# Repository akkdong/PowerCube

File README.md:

PowerCube
- Power Bank
- GPS
- Variometer
- Bluetooth

Goal: Charge mobile phone while transmitting GPS & Variometer data. It can also support BT connectivity.

<br>
<br>
<center>

</center>

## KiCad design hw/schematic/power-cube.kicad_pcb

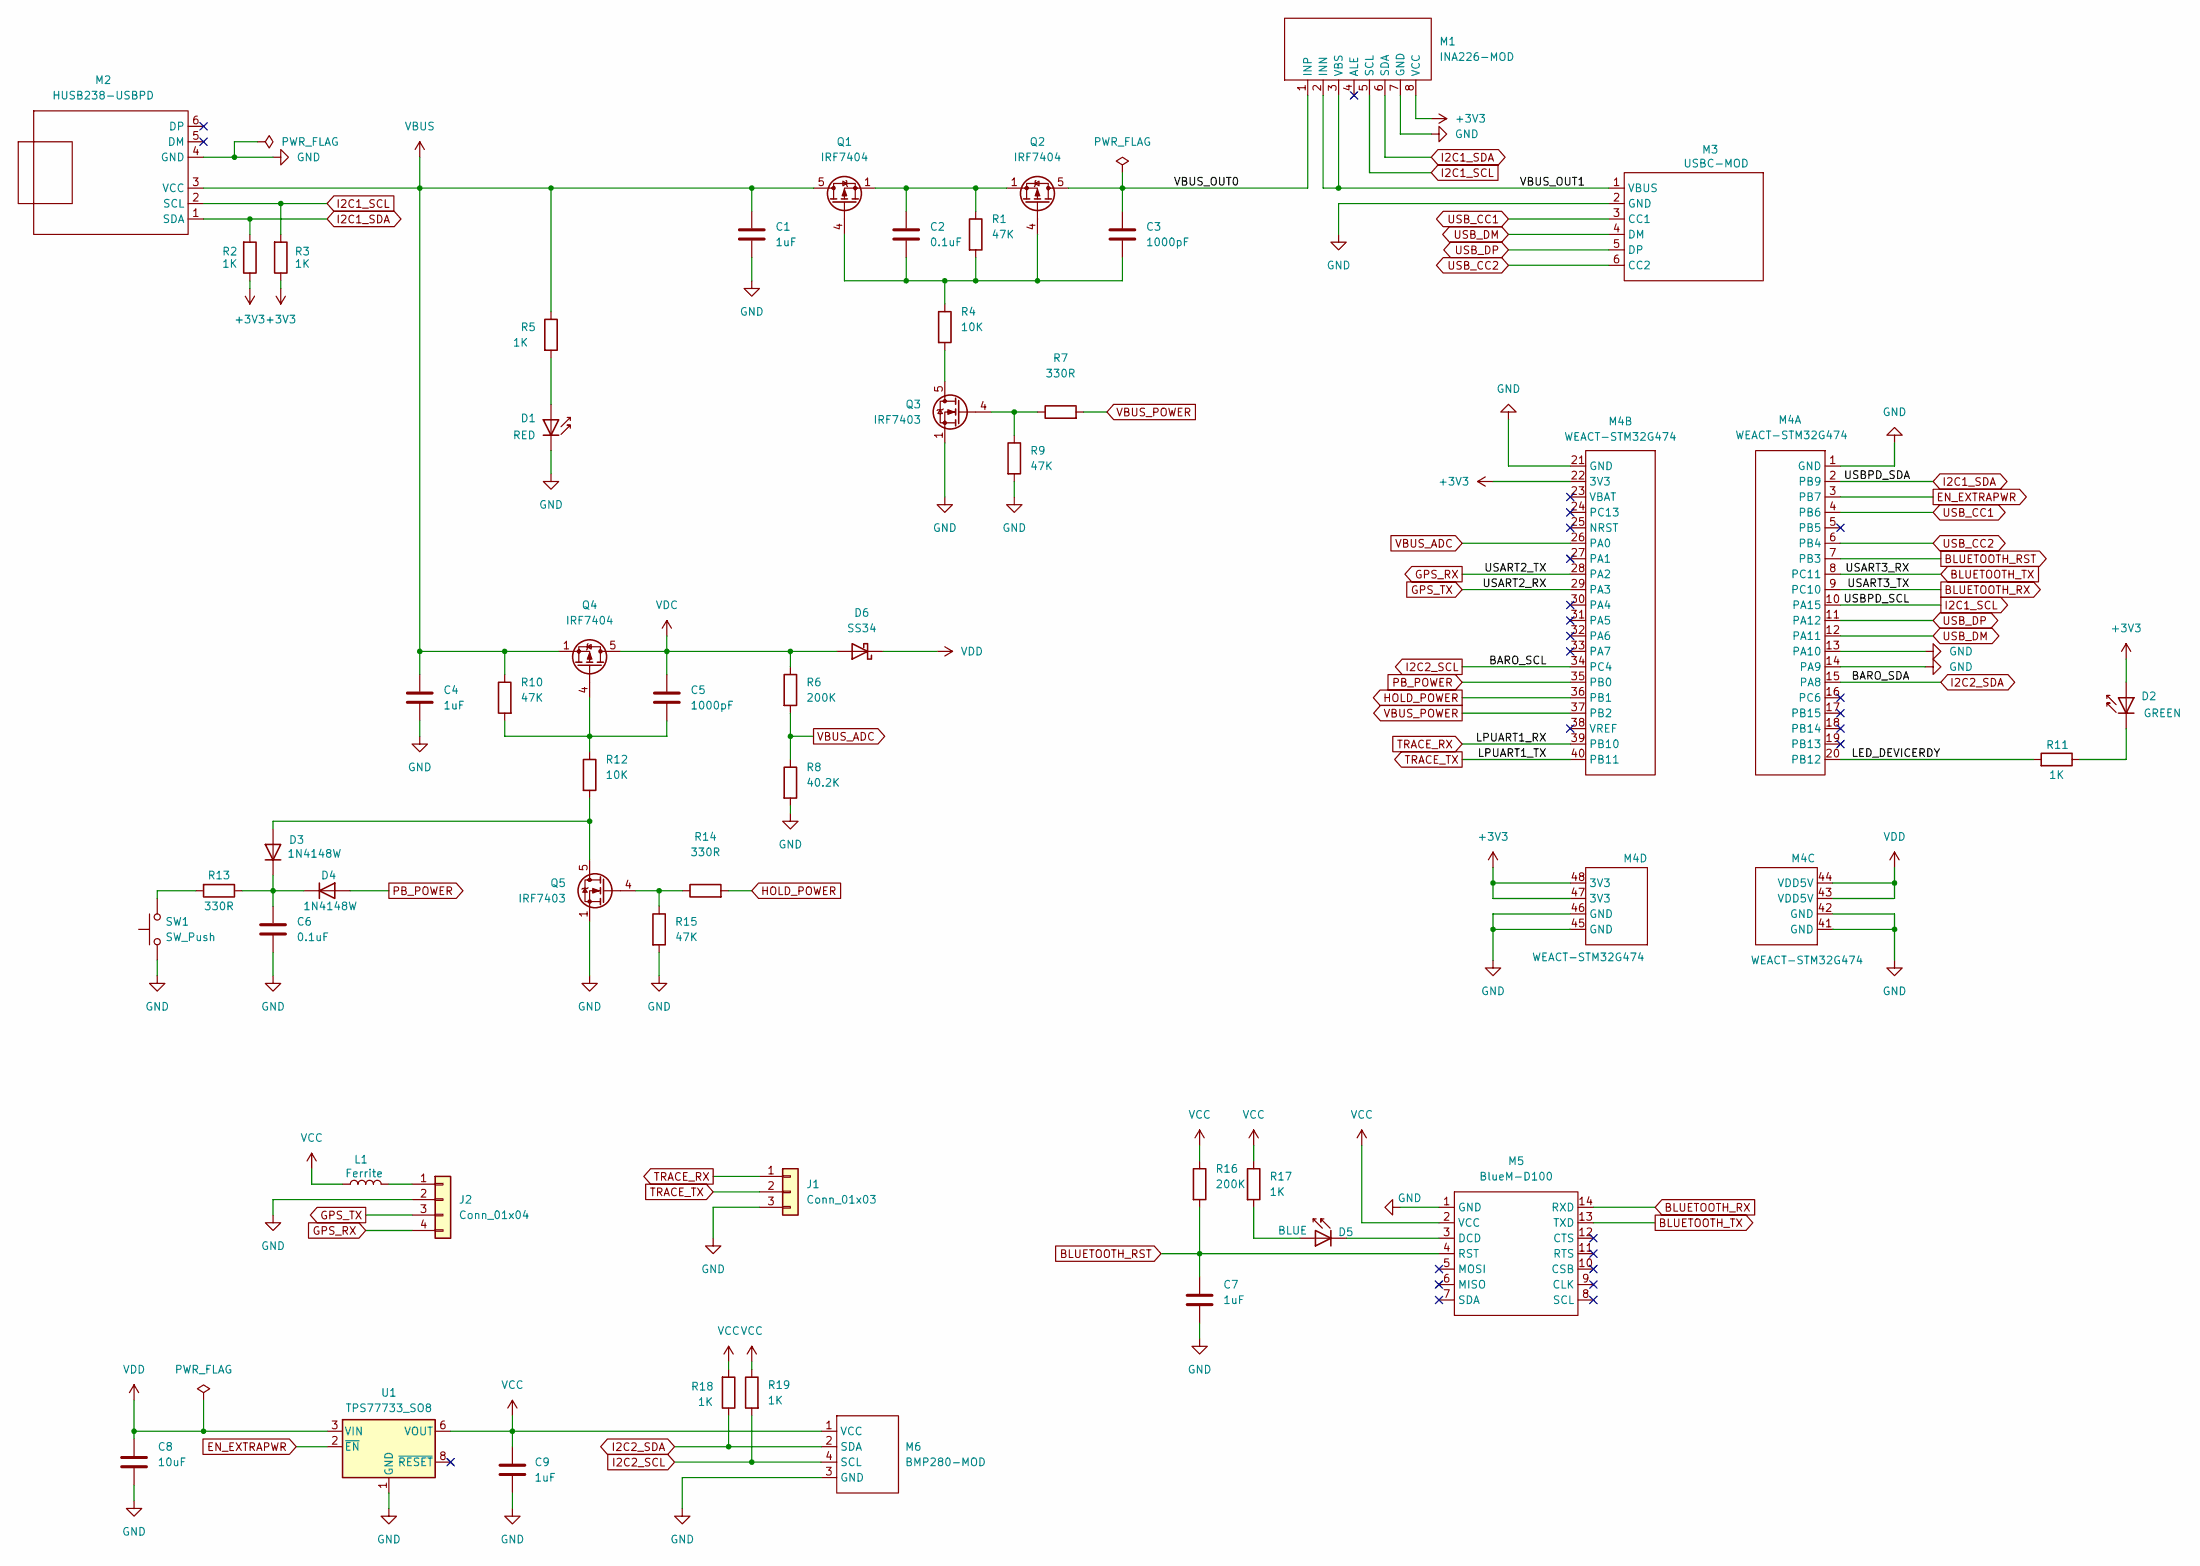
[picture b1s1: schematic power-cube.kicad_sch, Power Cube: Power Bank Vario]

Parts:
C1, C4, C7, C9: 1uF; C_0805_2012Metric_Pad1.18x1.45mm_HandSolder
C2, C6: 0.1uF; C_0805_2012Metric_Pad1.18x1.45mm_HandSolder
C3, C5: 1000pF; C_0805_2012Metric_Pad1.18x1.45mm_HandSolder
C8: 10uF; C_0805_2012Metric_Pad1.18x1.45mm_HandSolder
D1: RED; LED_0805_2012Metric_Pad1.15x1.40mm_HandSolder
D2: GREEN; LED_D3.0mm_Horizontal_O1.27mm_Z6.0mm
D3, D4: 1N4148W; D_SOD-123
D5: BLUE; LED_0805_2012Metric_Pad1.15x1.40mm_HandSolder
D6: SS34; D_SMA
J1: Conn_01x03; PinHeader_1x03_P2.54mm_Vertical
J2: Conn_01x04; GOOUUU-GPS-BD
L1: Ferrite; L_Axial_L5.3mm_D2.2mm_P10.16mm_Horizontal_Vishay_IM-1
M1: INA226-MOD
M2: HUSB238-USBPD
M3: USBC-MOD
M4: WEACT-STM32G474; WEACT-STM32G747
M5: BlueM-D100
M6: BMP280-MOD
Q1, Q2, Q4: IRF7404; DIP-8_W7.62mm_Socket
Q3, Q5: IRF7403; DIP-8_W7.62mm_Socket
R1, R9, R10, R15: 47K; R_0805_2012Metric_Pad1.20x1.40mm_HandSolder
R2, R3, R5, R11, R17, R18, R19: 1K; R_0805_2012Metric_Pad1.20x1.40mm_HandSolder
R4, R12: 10K; R_0805_2012Metric_Pad1.20x1.40mm_HandSolder
R6, R16: 200K; R_0805_2012Metric_Pad1.20x1.40mm_HandSolder
R7, R13, R14: 330R; R_0805_2012Metric_Pad1.20x1.40mm_HandSolder
R8: 40.2K; R_0805_2012Metric_Pad1.20x1.40mm_HandSolder
SW1: SW_Push; SW_Tactile_SPST_Angled_PTS645Vx39-2LFS
U1: TPS77733_SO8; DIP-8_W7.62mm_Socket

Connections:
+3V3: D2.2 (A), M1.8 (VCC), M4.22 (3V3), M4.47 (3V3), M4.48 (3V3), R2.1, R3.1
/LED_DEVICERDY: M4.20 (PB12), R11.2
/VBUS_OUT0: C3.2, M1.1 (INP), Q2.5 (D), Q2.6 (D), Q2.7 (D), Q2.8 (D)
/VBUS_OUT1: M1.2 (INN), M1.3 (VBS), M3.1 (VBUS)
BLUETOOTH_RST: C7.2, M4.7 (PB3), M5.4 (RST), R16.2
BLUETOOTH_RX: M4.9 (PC10), M5.14 (RXD)
BLUETOOTH_TX: M4.8 (PC11), M5.13 (TXD)
EN_EXTRAPWR: M4.3 (PB7), U1.2 (~EN)
GND: C1.1, C4.1, C6.1, C7.1, C8.1, C9.1, D1.1 (K), J1.3, J2.2, M1.7 (GND), M2.4 (GND), M3.2 (GND), M4.1 (GND), M4.13 (PA10), M4.14 (PA9), M4.21 (GND), M4.41 (GND), M4.42 (GND), M4.45 (GND), M4.46 (GND), M5.1 (GND), M6.3 (GND), Q3.1 (S), Q3.2 (S), Q3.3 (S), Q5.1 (S), Q5.2 (S), Q5.3 (S), R8.2, R9.2, R15.2, SW1.1, U1.1 (GND)
GPS_RX: J2.4, M4.28 (PA2)
GPS_TX: J2.3, M4.29 (PA3)
HOLD_POWER: M4.36 (PB1), R14.2
I2C1_SCL: M1.5 (SCL), M2.2 (SCL), M4.10 (PA15), R3.2
I2C1_SDA: M1.6 (SDA), M2.1 (SDA), M4.2 (PB9), R2.2
I2C2_SCL: M4.34 (PC4), M6.4 (SCL), R19.2
I2C2_SDA: M4.15 (PA8), M6.2 (SDA), R18.1
unnamed: C2.2, Q1.1 (S), Q1.2 (S), Q1.3 (S), Q2.1 (S), Q2.2 (S), Q2.3 (S), R1.1
unnamed: D1.2 (A), R5.2
unnamed: D2.1 (K), R11.1
unnamed: D3.2 (A), Q5.5 (D), Q5.6 (D), Q5.7 (D), Q5.8 (D), R12.2
unnamed: C6.2, D3.1 (K), D4.1 (K), R13.1
unnamed: D5.2 (A), R17.2
unnamed: D5.1 (K), M5.3 (DCD)
unnamed: J2.1, L1.1
unnamed: C2.1, C3.1, Q1.4 (G), Q2.4 (G), R1.2, R4.1
unnamed: Q3.5 (D), Q3.6 (D), Q3.7 (D), Q3.8 (D), R4.2
unnamed: Q3.4 (G), R7.1, R9.1
unnamed: C5.1, Q4.4 (G), R10.2, R12.1
unnamed: Q5.4 (G), R14.1, R15.1
unnamed: R13.2, SW1.2
PB_POWER: D4.2 (A), M4.35 (PB0)
TRACE_RX: J1.1, M4.39 (PB10)
TRACE_TX: J1.2, M4.40 (PB11)
USB_CC1: M3.3 (CC1), M4.4 (PB6)
USB_CC2: M3.6 (CC2), M4.6 (PB4)
USB_DM: M3.4 (DM), M4.12 (PA11)
USB_DP: M3.5 (DP), M4.11 (PA12)
VBUS: C1.2, C4.2, M2.3 (VCC), Q1.5 (D), Q1.6 (D), Q1.7 (D), Q1.8 (D), Q4.1 (S), Q4.2 (S), Q4.3 (S), R5.1, R10.1
VBUS_ADC: M4.26 (PA0), R6.2, R8.1
VBUS_POWER: M4.37 (PB2), R7.2
VCC: C9.2, L1.2, M5.2 (VCC), M6.1 (VCC), R16.1, R17.1, R18.2, R19.1, U1.5 (VOUT), U1.6 (VOUT)
VDC: C5.2, D6.2 (A), Q4.5 (D), Q4.6 (D), Q4.7 (D), Q4.8 (D), R6.1
VDD: C8.2, D6.1 (K), M4.43 (VDD5V), M4.44 (VDD5V), U1.3 (VIN), U1.4 (VIN)

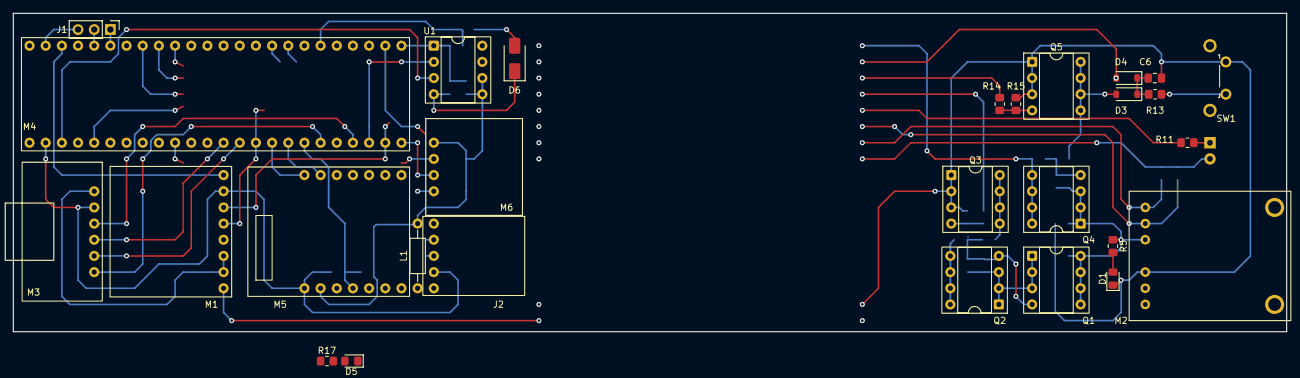
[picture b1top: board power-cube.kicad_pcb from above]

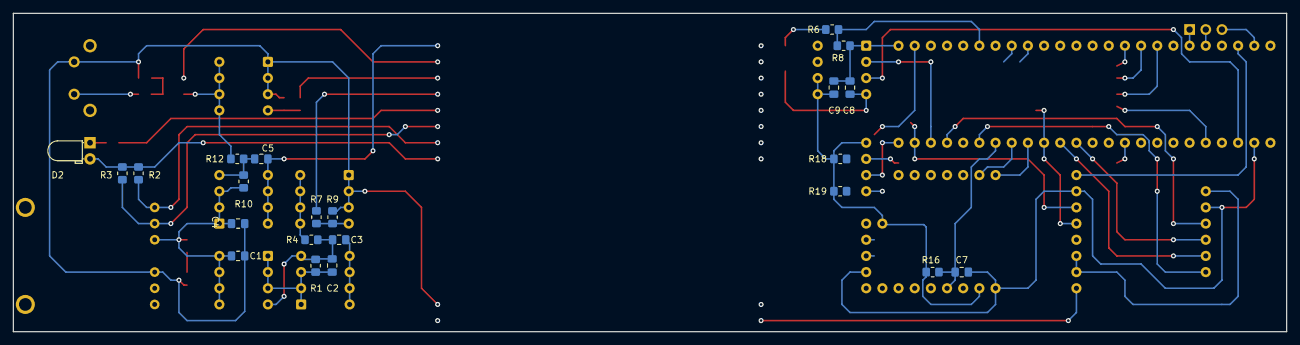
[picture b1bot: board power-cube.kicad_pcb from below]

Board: 2 copper layers, 200.0 x 50.0 mm, 50 parts (22 on the bottom side), 43 nets.

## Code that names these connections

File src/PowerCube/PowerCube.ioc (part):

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Mcu.Name=STM32G474C(B-C-E)Ux
Mcu.Package=UFQFPN48
Mcu.UserName=STM32G474CEUx
PA0.GPIOParameters=GPIO_Label
PA0.GPIO_Label=VBUS_ADC
PA0.Mode=IN1-Single-Ended
PA0.Signal=ADC1_IN1
PA10.Mode=EnableDeadBattery
PA10.Signal=UCPD1_DBCC2
PA11.Mode=Device
PA11.Signal=USB_DM
PA12.Mode=Device
PA12.Signal=USB_DP
PA13.Mode=Serial_Wire
PA13.Signal=SYS_JTMS-SWDIO
PA14.Mode=Serial_Wire
PA14.Signal=SYS_JTCK-SWCLK
PA15.GPIOParameters=GPIO_Label
PA15.GPIO_Label=USBPD_I2C_SCL
PA15.Mode=I2C
PA15.Signal=I2C1_SCL
PA2.GPIOParameters=GPIO_Label
PA2.GPIO_Label=GPS_RX
PA2.Mode=Asynchronous
PA2.Signal=USART2_TX
PA3.GPIOParameters=GPIO_Label
PA3.GPIO_Label=GPS_TX
PA3.Mode=Asynchronous
PA3.Signal=USART2_RX
PA8.GPIOParameters=GPIO_Label
PA8.GPIO_Label=BARO_I2C_SDA
PA8.Mode=I2C
PA8.Signal=I2C2_SDA
PA9.Mode=EnableDeadBattery
PA9.Signal=UCPD1_DBCC1
PB0.GPIOParameters=GPIO_PuPd,GPIO_Label,GPIO_ModeDefaultEXTI
PB0.GPIO_Label=PB_POWER
PB0.GPIO_ModeDefaultEXTI=GPIO_MODE_IT_RISING_FALLING
PB0.GPIO_PuPd=GPIO_PULLUP
PB0.Signal=GPXTI0
PB1.GPIOParameters=GPIO_Label
PB1.GPIO_Label=HOLD_POWER
PB1.Signal=GPIO_Output
PB10.GPIOParameters=GPIO_Label
PB10.GPIO_Label=TRACE_RX
PB10.Mode=Asynchronous
PB10.Signal=LPUART1_RX
PB11.GPIOParameters=GPIO_Label
PB11.GPIO_Label=TRACE_TX
PB11.Mode=Asynchronous
PB11.Signal=LPUART1_TX
PB12.GPIOParameters=PinState,GPIO_PuPd,GPIO_Label,GPIO_ModeDefaultOutputPP
PB12.GPIO_Label=LED_DEVICERDY
PB12.GPIO_ModeDefaultOutputPP=GPIO_MODE_OUTPUT_OD
PB12.GPIO_PuPd=GPIO_NOPULL
PB12.PinState=GPIO_PIN_SET
PB12.Signal=GPIO_Output
PB2.GPIOParameters=GPIO_Label
PB2.GPIO_Label=VBUS_POWER
PB2.Signal=GPIO_Output
PB3.GPIOParameters=PinState,GPIO_PuPd,GPIO_Label,GPIO_ModeDefaultOutputPP
PB3.GPIO_Label=BLUETOOTH_RST
PB3.GPIO_ModeDefaultOutputPP=GPIO_MODE_OUTPUT_PP
PB3.GPIO_PuPd=GPIO_NOPULL
PB3.PinState=GPIO_PIN_SET
PB3.Signal=GPIO_Output
PB4.Mode=Source_AllSignals
PB4.Signal=UCPD1_CC2
PB6.Mode=Source_AllSignals
PB6.Signal=UCPD1_CC1
PB7.GPIOParameters=PinState,GPIO_PuPd,GPIO_Label
PB7.GPIO_Label=EN_EXTRAPWR
PB7.GPIO_PuPd=GPIO_PULLUP
PB7.PinState=GPIO_PIN_SET
PB7.Signal=GPIO_Output
PB9.GPIOParameters=GPIO_Label
PB9.GPIO_Label=USBPD_I2C_SDA
PB9.Mode=I2C
PB9.Signal=I2C1_SDA
PC10.GPIOParameters=GPIO_Label
PC10.GPIO_Label=BLUETOOTH_RX
PC10.Mode=Asynchronous
PC10.Signal=USART3_TX
PC11.GPIOParameters=GPIO_Label
PC11.GPIO_Label=BLUETOOTH_TX
PC11.Mode=Asynchronous
PC11.Signal=USART3_RX
PC13.GPIOParameters=GPIO_PuPd,GPIO_Label,GPIO_ModeDefaultEXTI
PC13.GPIO_Label=PB_BOARD
PC13.GPIO_ModeDefaultEXTI=GPIO_MODE_IT_RISING_FALLING
PC13.GPIO_PuPd=GPIO_PULLDOWN
PC13.Signal=GPXTI13
PC14-OSC32_IN.Mode=LSE-External-Oscillator
PC14-OSC32_IN.Signal=RCC_OSC32_IN
PC15-OSC32_OUT.Mode=LSE-External-Oscillator
PC15-OSC32_OUT.Signal=RCC_OSC32_OUT
PC4.GPIOParameters=GPIO_Label
PC4.GPIO_Label=BARO_I2C_SCL
PC4.Mode=I2C
PC4.Signal=I2C2_SCL
PC6.GPIOParameters=GPIO_Label
PC6.GPIO_Label=LED_BOARD
PC6.Signal=GPIO_Output
PF0-OSC_IN.Mode=HSE-External-Oscillator
PF0-OSC_IN.Signal=RCC_OSC_IN
PF1-OSC_OUT.Mode=HSE-External-Oscillator
PF1-OSC_OUT.Signal=RCC_OSC_OUT
RCC.HSE_VALUE=8000000
RCC.SYSCLKFreq_VALUE=144000000
RCC.SYSCLKSource=RCC_SYSCLKSOURCE_PLLCLK
board=custom

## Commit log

2025-11-30 readme
2025-11-30 more document & link
2025-12-01 update pdf schematic
2025-12-01 mod schematic
2025-12-01 add extra-power enable
2025-12-01 add reference
2025-12-07 add source
2025-12-07 fixed build error
2025-12-08 c --> c++
2025-12-08 sensor: BMP280, INA226
2025-12-08 husb238 register information
2025-12-08 husb238 usb-pd sink controller
2025-12-09 task
2025-12-10 sensor AHT20 (un-tested) BT handler (TBD) fixed RTOS configuration
2025-12-10 usbpd implement (TBD, not working)
2025-12-11 monitor app basic
2025-12-11 usbpd implement (TBD)
2025-12-11 usbpd implment (TBD)
2025-12-12 Implement USBPD basic function
    - Supply Fixed 5V
    - UFP date role swap --> Virtual COM Device
2025-12-13 use message-q
2025-12-13 vario stubs
2025-12-13 make & transfer vario sentence
2025-12-13 add nmea parser
2025-12-14 usb2serial : clone of Arduino
2025-12-14 rename USBD_XXX
2025-12-15 migrate to TCPP 4.2.0
    - usbpd & utilities (GUI_INTEFACE, TRACER_EMB)
    - change task priority to make GUI work
2025-12-15 screen-shot
2025-12-15 screen-shots
    Added images to README for better visualization.
2025-12-15 Fix typo
2025-12-17 enclosure (TBD)
2025-12-17 add missing file
2025-12-17 remove file
2025-12-19 Add case layout image to README
2025-12-21 use ucpd as debugging port
2025-12-22 MSC bootloader
2025-12-22 change volume/storage name
2025-12-23 references
2025-12-24 confirm F/W version by MSC version.txt
2025-12-27 enclosure (done)
2025-12-27 install.jpg
2026-01-02 Minor update - bootloader: enter user application if there is no action - increase buffer/heap size - wait baro wake up
2026-01-06 hold down power key when booting
